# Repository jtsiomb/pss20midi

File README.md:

YAMAHA PSS-20 MIDI conversion
=============================

About
-----
This is a replacement board for the YAMAHA PSS-20 vintage toy keyboard, which
converts it into a polyphonic MIDI keyboard.

License
-------
Copyright (C) 2024 John Tsiombikas <nuclear@mutantstargoat.com>,
                   Eleni-Maria Stea <elene.mst@gmail.com>

All parts of this project are Free Software/Hardware. Feel free to use, modify
and/or redistribute under the terms of the GNU General Public License v3, or at
your option any later version published by the Free Software Foundation. See
COPYING for details.

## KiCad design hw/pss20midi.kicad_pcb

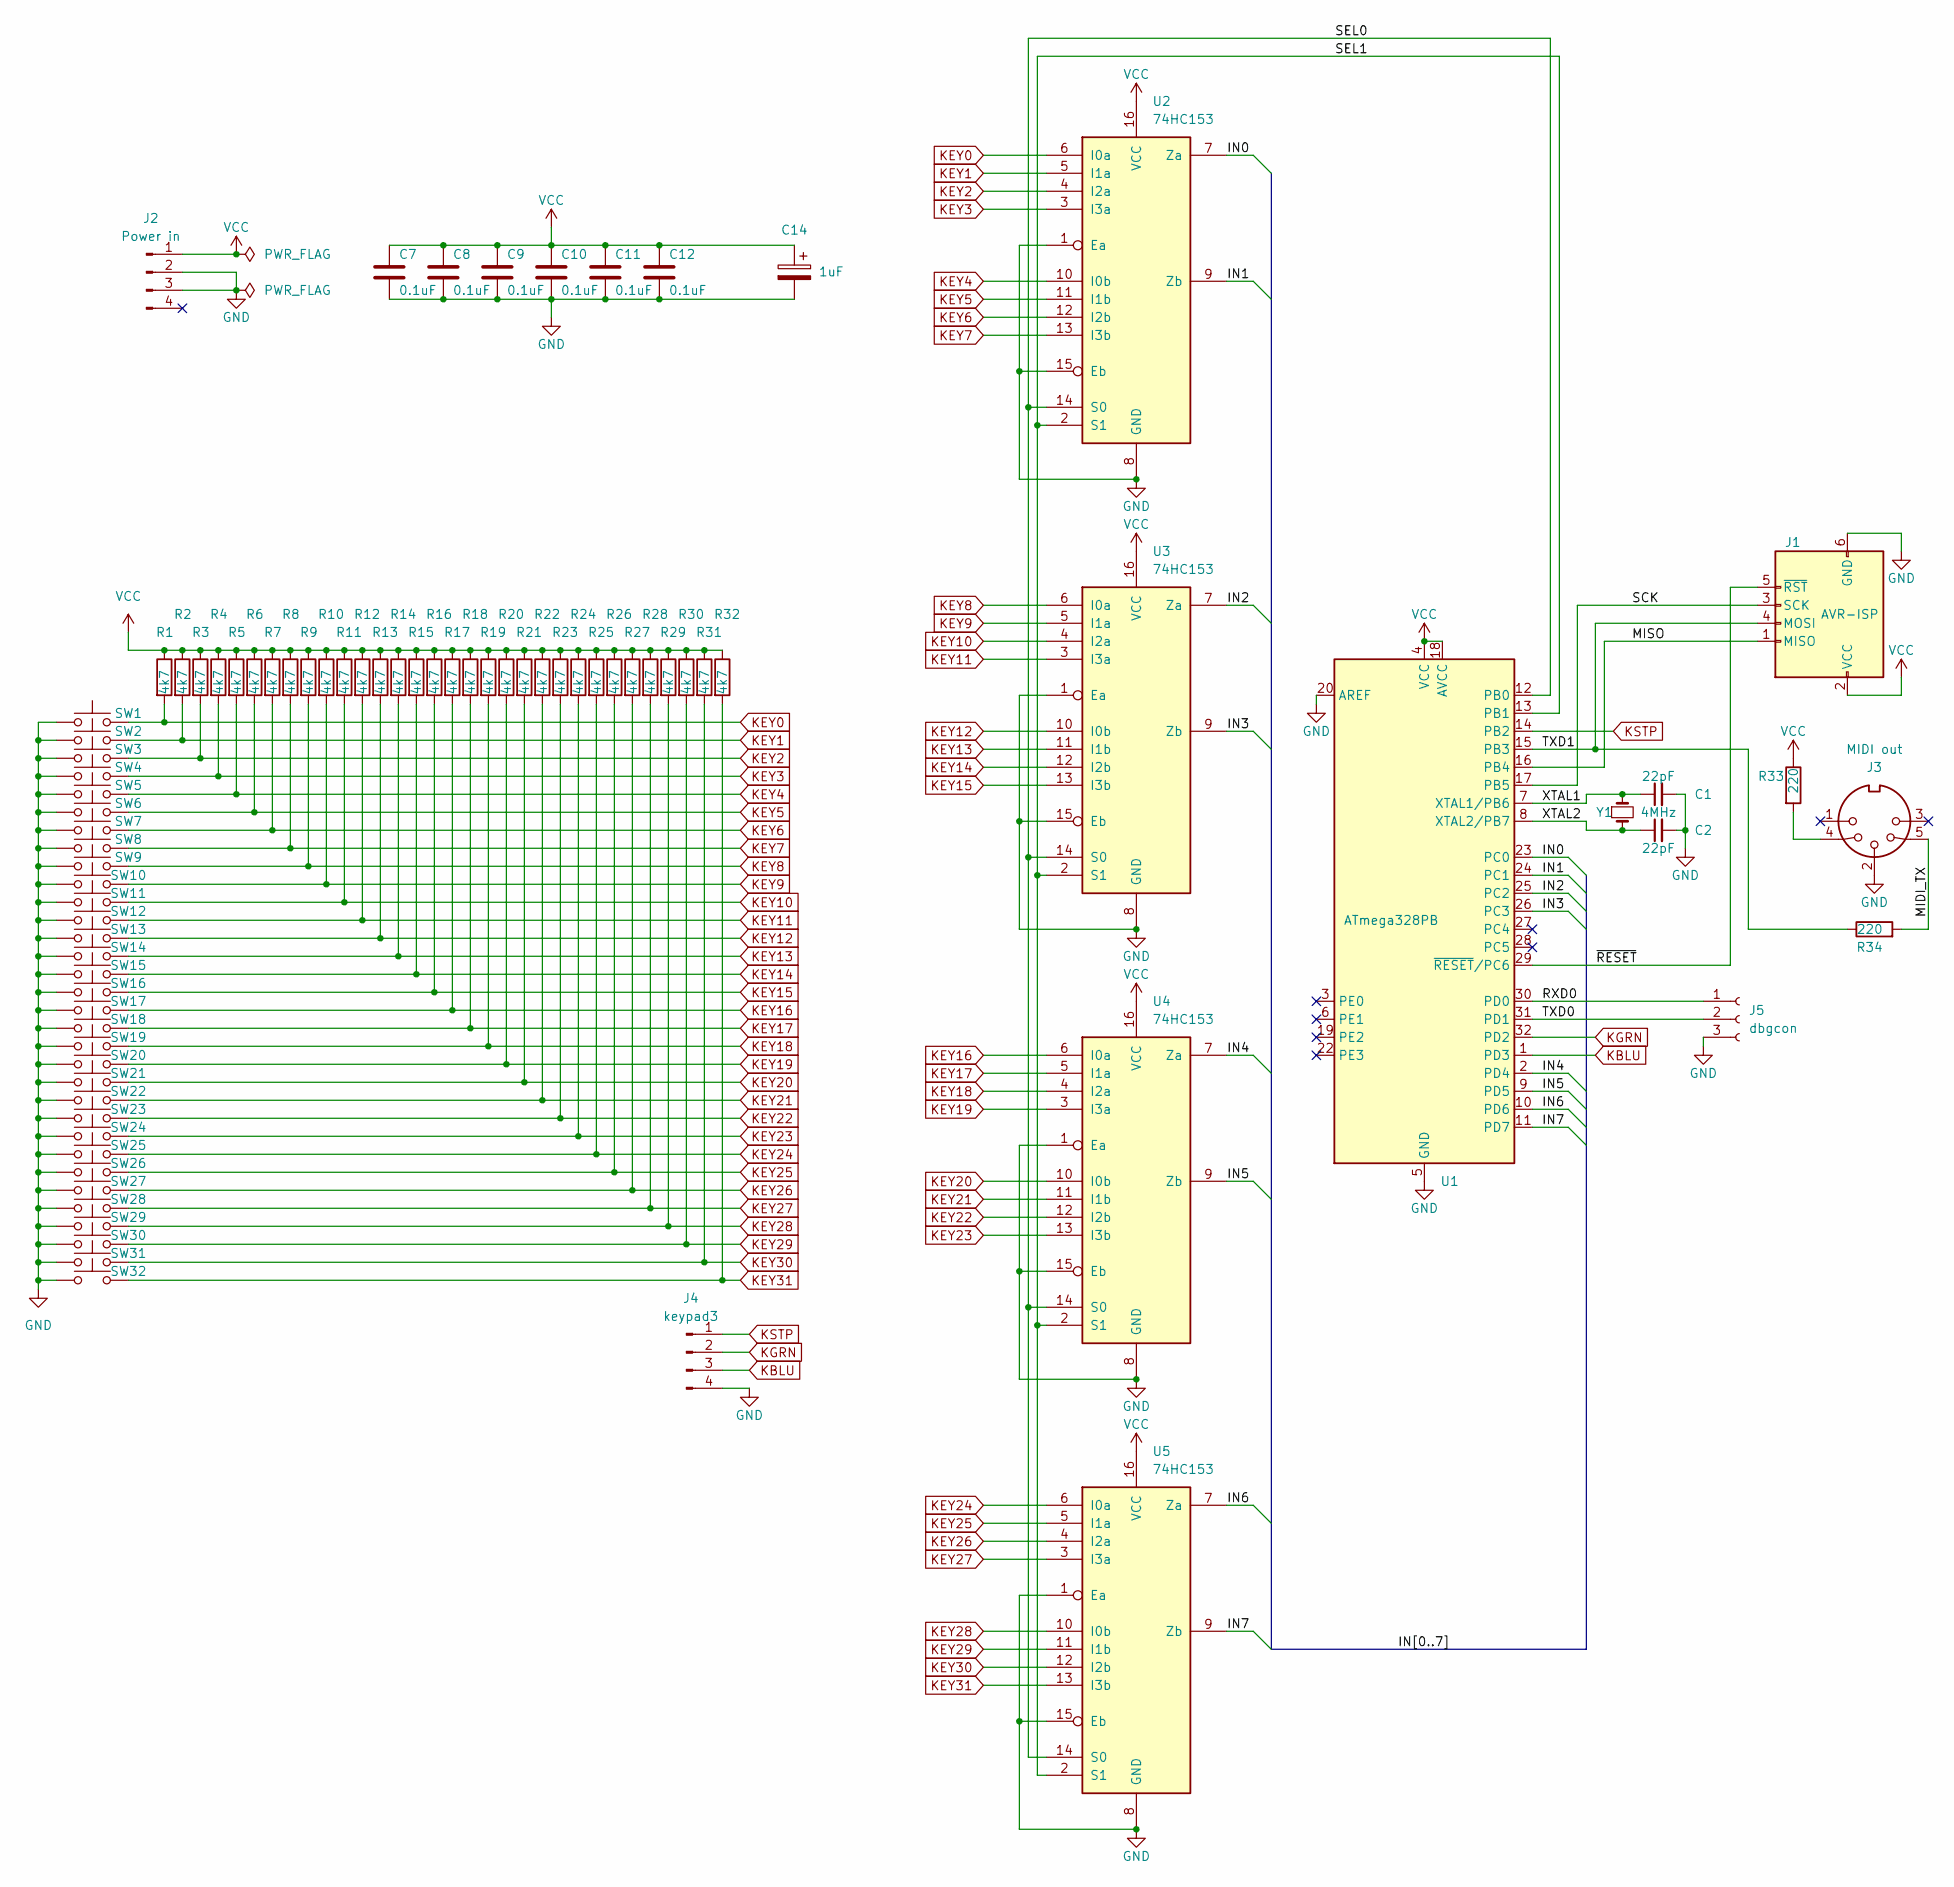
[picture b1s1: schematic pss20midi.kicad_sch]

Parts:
C1, C2: 22pF; C_0805_2012Metric_Pad1.18x1.45mm_HandSolder
C7, C8, C9, C10, C11, C12: 0.1uF; C_0805_2012Metric_Pad1.18x1.45mm_HandSolder
C14: 1uF; CP_Elec_4x5.4
J1: AVR-ISP; IDC-Header_2x03_P2.54mm_Vertical
J2: Power in; PinHeader_1x04_P2.54mm_Horizontal
J3: MIDI out; PinHeader_1x05_P2.54mm_Horizontal
J4: keypad3; PinHeader_1x04_P2.54mm_Horizontal
J5: dbgcon; PinSocket_1x03_P2.54mm_Horizontal
R1, R2, R3, R4, R5, R6, R7, R8, R9, R10, R11, R12, R13, R14, R15, R16, R17, R18, R19, R20, R21, R22, R23, R24, R25, R26, R27, R28, R29, R30, R31, R32: 4k7; R_0805_2012Metric_Pad1.20x1.40mm_HandSolder
R33, R34: 220; R_0805_2012Metric_Pad1.20x1.40mm_HandSolder
SW1, SW2, SW3, SW4, SW5, SW6, SW7, SW8, SW9, SW10, SW11, SW12, SW13, SW14, SW15, SW16, SW17, SW18, SW19, SW20, SW21, SW22, SW23, SW24, SW25, SW26, SW27, SW28, SW29, SW30, SW31, SW32: SW_Push; bncontact
U1: ATmega328PB; TQFP-32_7x7mm_P0.8mm
U2, U3, U4, U5: 74HC153; SOIC-16_3.9x9.9mm_P1.27mm
Y1: 4MHz; Crystal_SMD_HC49-SD

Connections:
/IN0: U1.23 (PC0), U2.7 (Za)
/IN1: U1.24 (PC1), U2.9 (Zb)
/IN2: U1.25 (PC2), U3.7 (Za)
/IN3: U1.26 (PC3), U3.9 (Zb)
/IN4: U1.2 (PD4), U4.7 (Za)
/IN5: U1.9 (PD5), U4.9 (Zb)
/IN6: U1.10 (PD6), U5.7 (Za)
/IN7: U1.11 (PD7), U5.9 (Zb)
/MIDI_TX: J3.5, R34.2
/MISO: J1.1 (MISO), U1.16 (PB4)
/RXD0: J5.1, U1.30 (PD0)
/SCK: J1.3 (SCK), U1.17 (PB5)
/SEL0: U1.12 (PB0), U2.14 (S0), U3.14 (S0), U4.14 (S0), U5.14 (S0)
/SEL1: U1.13 (PB1), U2.2 (S1), U3.2 (S1), U4.2 (S1), U5.2 (S1)
/TXD0: J5.2, U1.31 (PD1)
/TXD1: J1.4 (MOSI), R34.1, U1.15 (PB3)
/XTAL1: C1.1, U1.7 (XTAL1/PB6), Y1.1
/XTAL2: C2.1, U1.8 (XTAL2/PB7), Y1.2
/~RESET: J1.5 (~RST), U1.29 (~RESET/PC6)
GND: C1.2, C2.2, C7.2, C8.2, C9.2, C10.2, C11.2, C12.2, C14.2, J1.6 (GND), J2.2, J2.3, J3.2, J4.4, J5.3, SW1.1, SW2.1, SW3.1, SW4.1, SW5.1, SW6.1, SW7.1, SW8.1, SW9.1, SW10.1, SW11.1, SW12.1, SW13.1, SW14.1, SW15.1, SW16.1, SW17.1, SW18.1, SW19.1, SW20.1, SW21.1, SW22.1, SW23.1, SW24.1, SW25.1, SW26.1, SW27.1, SW28.1, SW29.1, SW30.1, SW31.1, SW32.1, U1.5 (GND), U1.20 (AREF), U1.21 (GND), U2.1 (Ea), U2.8 (GND), U2.15 (Eb), U3.1 (Ea), U3.8 (GND), U3.15 (Eb), U4.1 (Ea), U4.8 (GND), U4.15 (Eb), U5.1 (Ea), U5.8 (GND), U5.15 (Eb)
KBLU: J4.3, U1.1 (PD3)
KEY0: R1.2, SW1.2, U2.6 (I0a)
KEY1: R2.2, SW2.2, U2.5 (I1a)
KEY2: R3.2, SW3.2, U2.4 (I2a)
KEY3: R4.2, SW4.2, U2.3 (I3a)
KEY4: R5.2, SW5.2, U2.10 (I0b)
KEY5: R6.2, SW6.2, U2.11 (I1b)
KEY6: R7.2, SW7.2, U2.12 (I2b)
KEY7: R8.2, SW8.2, U2.13 (I3b)
KEY8: R9.2, SW9.2, U3.6 (I0a)
KEY9: R10.2, SW10.2, U3.5 (I1a)
KEY10: R11.2, SW11.2, U3.4 (I2a)
KEY11: R12.2, SW12.2, U3.3 (I3a)
KEY12: R13.2, SW13.2, U3.10 (I0b)
KEY13: R14.2, SW14.2, U3.11 (I1b)
KEY14: R15.2, SW15.2, U3.12 (I2b)
KEY15: R16.2, SW16.2, U3.13 (I3b)
KEY16: R17.2, SW17.2, U4.6 (I0a)
KEY17: R18.2, SW18.2, U4.5 (I1a)
KEY18: R19.2, SW19.2, U4.4 (I2a)
KEY19: R20.2, SW20.2, U4.3 (I3a)
KEY20: R21.2, SW21.2, U4.10 (I0b)
KEY21: R22.2, SW22.2, U4.11 (I1b)
KEY22: R23.2, SW23.2, U4.12 (I2b)
KEY23: R24.2, SW24.2, U4.13 (I3b)
KEY24: R25.2, SW25.2, U5.6 (I0a)
KEY25: R26.2, SW26.2, U5.5 (I1a)
KEY26: R27.2, SW27.2, U5.4 (I2a)
KEY27: R28.2, SW28.2, U5.3 (I3a)
KEY28: R29.2, SW29.2, U5.10 (I0b)
KEY29: R30.2, SW30.2, U5.11 (I1b)
KEY30: R31.2, SW31.2, U5.12 (I2b)
KEY31: R32.2, SW32.2, U5.13 (I3b)
KGRN: J4.2, U1.32 (PD2)
KSTP: J4.1, U1.14 (PB2)
unnamed: J3.4, R33.2
VCC: C7.1, C8.1, C9.1, C10.1, C11.1, C12.1, C14.1, J1.2 (VCC), J2.1, R1.1, R2.1, R3.1, R4.1, R5.1, R6.1, R7.1, R8.1, R9.1, R10.1, R11.1, R12.1, R13.1, R14.1, R15.1, R16.1, R17.1, R18.1, R19.1, R20.1, R21.1, R22.1, R23.1, R24.1, R25.1, R26.1, R27.1, R28.1, R29.1, R30.1, R31.1, R32.1, R33.1, U1.4 (VCC), U1.18 (AVCC), U2.16 (VCC), U3.16 (VCC), U4.16 (VCC), U5.16 (VCC)

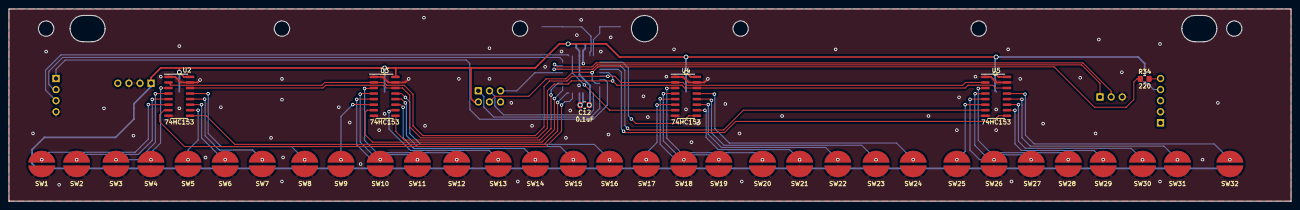
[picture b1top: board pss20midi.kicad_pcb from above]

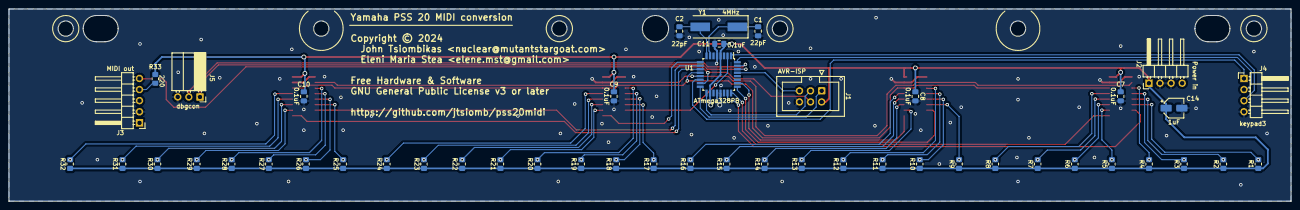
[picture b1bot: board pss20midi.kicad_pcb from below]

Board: 2 copper layers, 293.5 x 44.0 mm, 86 parts (48 on the bottom side), 57 nets.

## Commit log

2024-02-22 completed schematic and footprint assignment
2024-02-26 PCB done
2024-02-26 Added github url to the PCB silkscreen
2024-02-26 add gerbers
2024-02-26 readme
2024-03-10 Added midi events, key scanning, not tested yet
2024-03-10 minor code cleanup and debug output on UART0
2024-03-29 fixed MIDI voltage and polarity mistake
2024-03-29 bizarre reordering of they keymap to produce correct notes
2025-03-29 remove "untested" warning

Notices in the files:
hw/pss20midi.kicad_pcb:
Free Hardware & Software - GNU General Public License v3 or later
Copyright © 2024
hw/pss20midi.kicad_sch:
Free hardware & software - GNU GPLv3 or later
